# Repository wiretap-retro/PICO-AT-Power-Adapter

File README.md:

# PICO-AT Power Adapter
This board is a PICO-PSU to AT power adapter which also provides -5VDC.

## Intro
I designed this board for a small SBC that I could not fit a large power supply in the enclosure. This design is recommended for PICO-PSU units, and can be used with various retro motherboards that have the AT-style power connector. I have two versions in this repository, the normal version and a high current version. The high current version can be used with later model systems drawing more than 8 amps on the 5V rail. I recommend you don't go over 14 amps on the 5V rail with the high current version.

## Building
* Detailed BOM for Mouser parts is included. Subsitutions may be necessary depending on the chip/component shortages.
* Solder the SMD components first, then solder the through-hole components. The 7905 component will need to be flush clipped with the board before soldering, to ensure the ATX connector sits flat.
* Depending on your motherboard, this may not fit without modification to the motherboard's power connector. You will need to have the square pins on the power connector, not the larger round pins or flat pins. Most AT boards have the flat pins. See notes section below.

## Notes
* Molex only produced the flat style AT pin header (8619) for use with the 90331 power supply connectors. The flat pin 8619 style motherboard side connectors were only used on AT motherboards to a certain time period, then Molex discontinued the 8619 and replaced it with the KK 396 square pin connector, which is compatible with the 90331 connector as well as KK 396 female connectors, obviously. I only have one motherboard in my collection that came standard with the KK 396 connector. If the motherboard uses the old 8619 connector, it would need to be replaced with the KK 396 type. So, with the KK 396 compatible with both the 90331 and KK 396 itself, you lose no functionality with an original AT power supply connector. I have validated this with motherboards I have converted. The part number for the motherboard side is Molex 41791-0836. (2 required)
* The power switch pin header is for connecting a standard toggle switch to control the ATX power supply's on/off state. You can wire it to your AT case's power switch. In a modern PC case, you can wire it to a latching power switch or an on/off toggle switch. 

## Community Works
Check out Vogons.org for the thread where people are building these and also modifying the design to have fan headers and other cool stuff: https://www.vogons.org/viewtopic.php?f=46&t=86465

## Other
This is an open source design. Feel free to do what you want with it.

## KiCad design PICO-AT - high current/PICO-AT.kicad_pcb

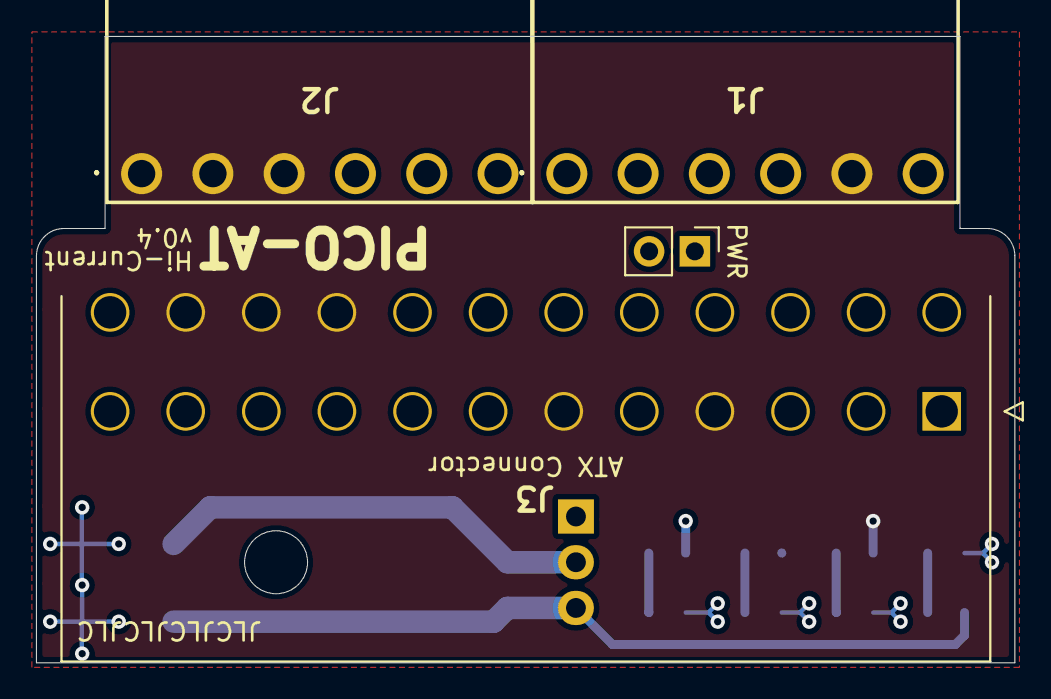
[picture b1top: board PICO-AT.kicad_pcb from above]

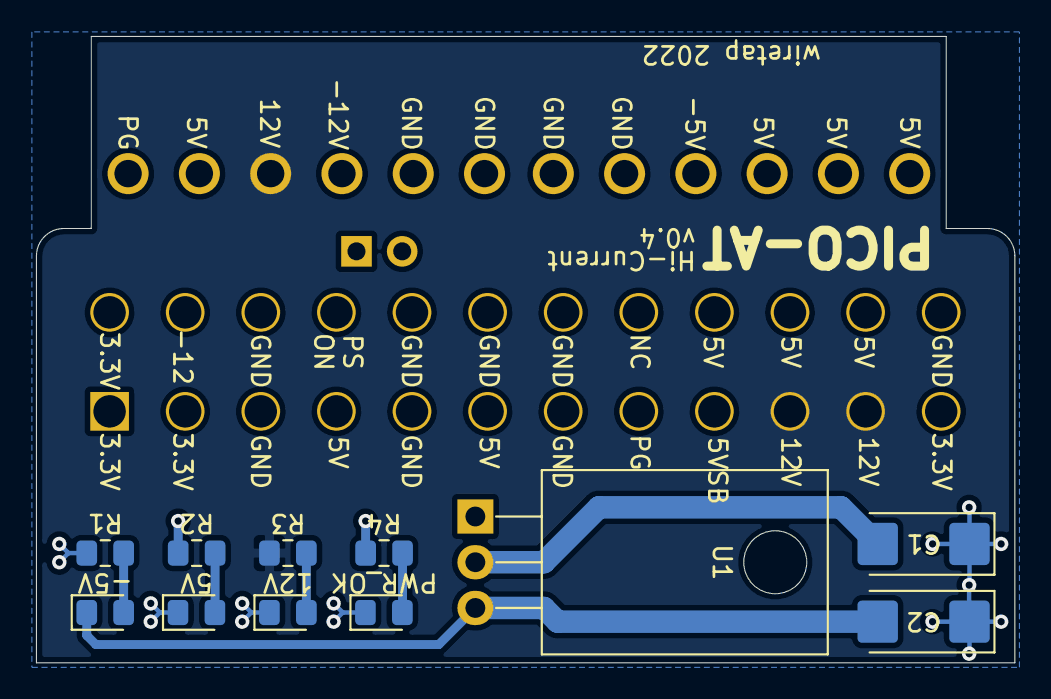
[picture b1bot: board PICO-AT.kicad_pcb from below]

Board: 4 copper layers, 54.4 x 34.8 mm, 15 parts (11 on the bottom side), 12 nets.

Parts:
5V, 12V: LED; LED_0805_2012Metric_Pad1.15x1.40mm_HandSolder
-5V: LED; LED_0805_2012Metric_Pad1.15x1.40mm_HandSolder
C1: 2.2uF; CP_EIA-6032-28_Kemet-C_Pad2.25x2.35mm_HandSolder
C2: 1uF; CP_EIA-6032-28_Kemet-C_Pad2.25x2.35mm_HandSolder
J1, J2: 09-48-1064; 09481064
J3: 87427-2402
PWR: PWR_SW; PinHeader_1x02_P2.54mm_Vertical
PWR_OK: LED; LED_0805_2012Metric_Pad1.15x1.40mm_HandSolder
R1, R2, R4: 330; R_0805_2012Metric_Pad1.15x1.40mm_HandSolder
R3: 1k; R_0805_2012Metric_Pad1.15x1.40mm_HandSolder
U1: L7905; TO-220-3_Horizontal_TabDown

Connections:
/3.3V: J3.1, J3.2, J3.12, J3.13
/5V: J1.5, J2.1, J2.2, J2.3, J3.4, J3.6, J3.21, J3.22, J3.23, R2.1
/12V: J1.4, J3.10, J3.11, R3.1
/-5V: -5V.1, C2.2, J2.4, U1.3
/-12V: C1.2, J1.3, J3.14, U1.2
/GND: 5V.1, 12V.1, C1.1, C2.1, J1.1, J1.2, J2.5, J2.6, J3.3, J3.5, J3.7, J3.15, J3.17, J3.18, J3.19, J3.24, PWR.2, PWR_OK.1, R1.1, U1.1
/PG: J1.6, J3.8, R4.1
/PS-ON: J3.16, PWR.1
unnamed: -5V.2, R1.2
unnamed: 5V.2, R2.2
unnamed: 12V.2, R3.2
unnamed: PWR_OK.2, R4.2
